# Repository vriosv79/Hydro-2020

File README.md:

Respositorio para velocímetros con códigos y diseños de PCB

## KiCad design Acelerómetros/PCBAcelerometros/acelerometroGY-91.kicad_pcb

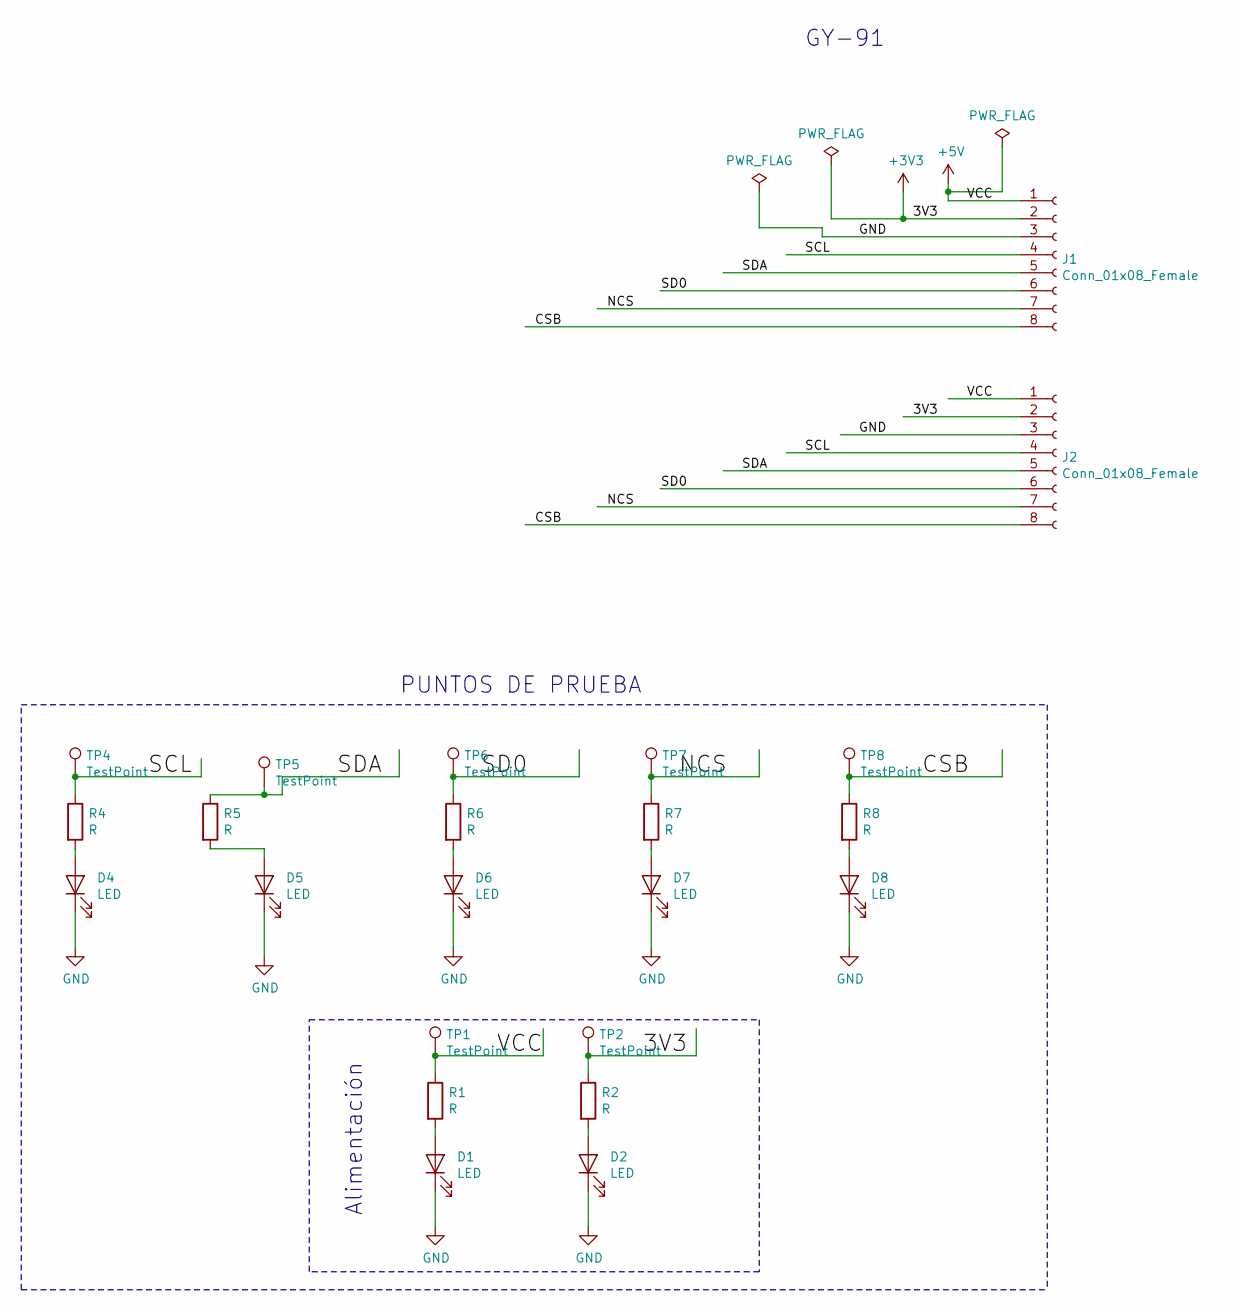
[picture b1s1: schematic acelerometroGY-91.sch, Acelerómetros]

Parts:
D1, D2, D4, D5, D6, D7, D8: LED; LED_0805_2012Metric
J1: Conn_01x08_Female; PinHeader_1x08_P2.54mm_Vertical
J2: Conn_01x08_Female; Molex_CLIK-Mate_502382-0870_1x08-1MP_P1.25mm_Vertical
R1, R2, R4, R5, R6, R7, R8: R; R_0805_2012Metric
TP1, TP2, TP4, TP5, TP6, TP7, TP8: TestPoint; TestPoint_Bridge_Pitch2.0mm_Drill0.7mm

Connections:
+3V3: J1.2, J2.2, R2.1, TP2.1
+5V: J1.1, J2.1, R1.1, TP1.1
/CSB: J1.8, J2.8, R8.1, TP8.1
/NCS: J1.7, J2.7, R7.1, TP7.1
/SCL: J1.4, J2.4, R4.1, TP4.1
/SD0: J1.6, J2.6, R6.1, TP6.1
/SDA: J1.5, J2.5, R5.1, TP5.1
GND: D1.1 (K), D2.1 (K), D4.1 (K), D5.1 (K), D6.1 (K), D7.1 (K), D8.1 (K), J1.3, J2.3
unnamed: D1.2 (A), R1.2
unnamed: D2.2 (A), R2.2
unnamed: D4.2 (A), R4.2
unnamed: D5.2 (A), R5.2
unnamed: D6.2 (A), R6.2
unnamed: D7.2 (A), R7.2
unnamed: D8.2 (A), R8.2

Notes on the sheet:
GY-91
PUNTOS DE PRUEBA
Alimentación

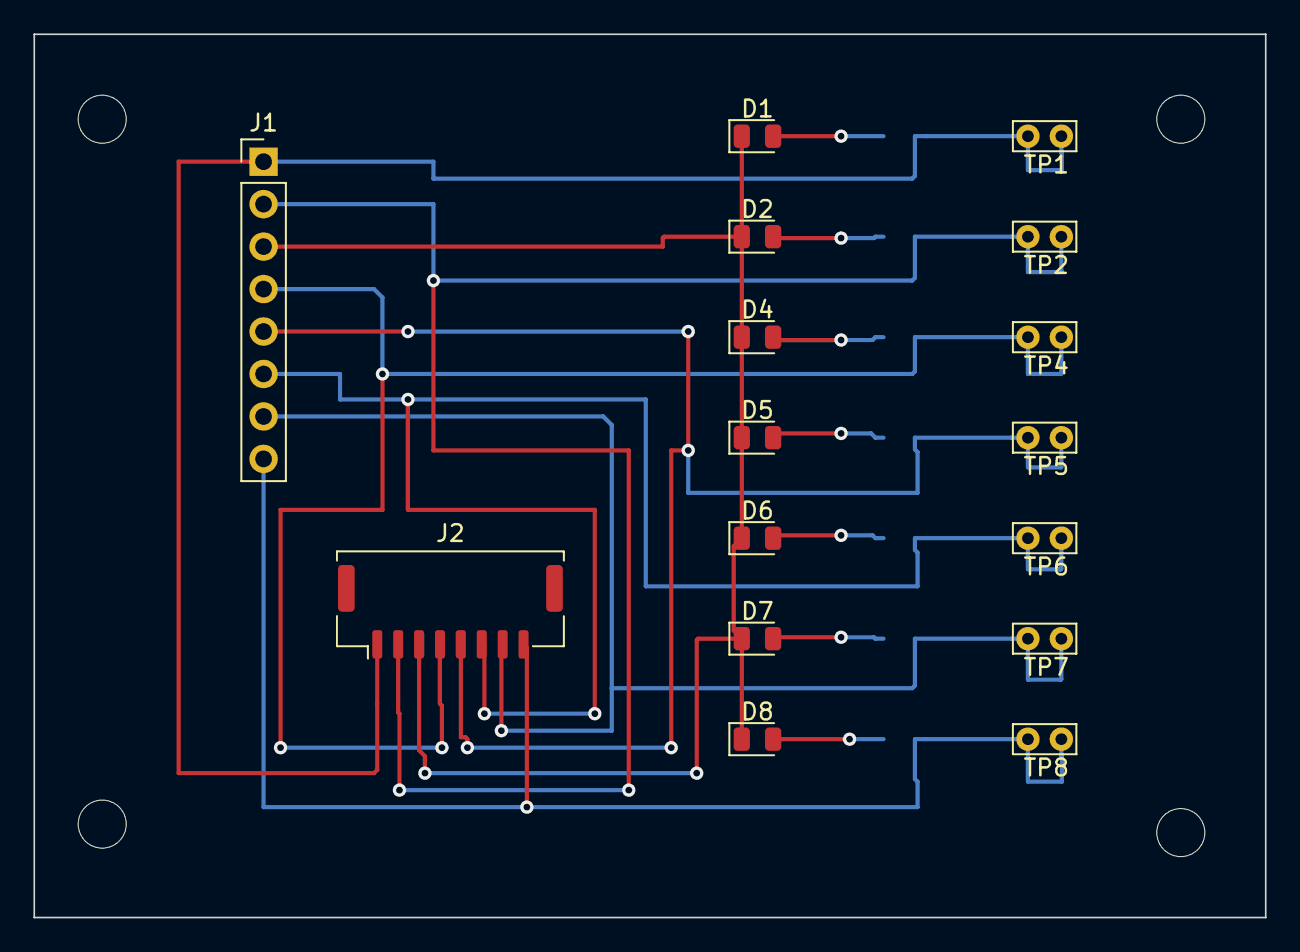
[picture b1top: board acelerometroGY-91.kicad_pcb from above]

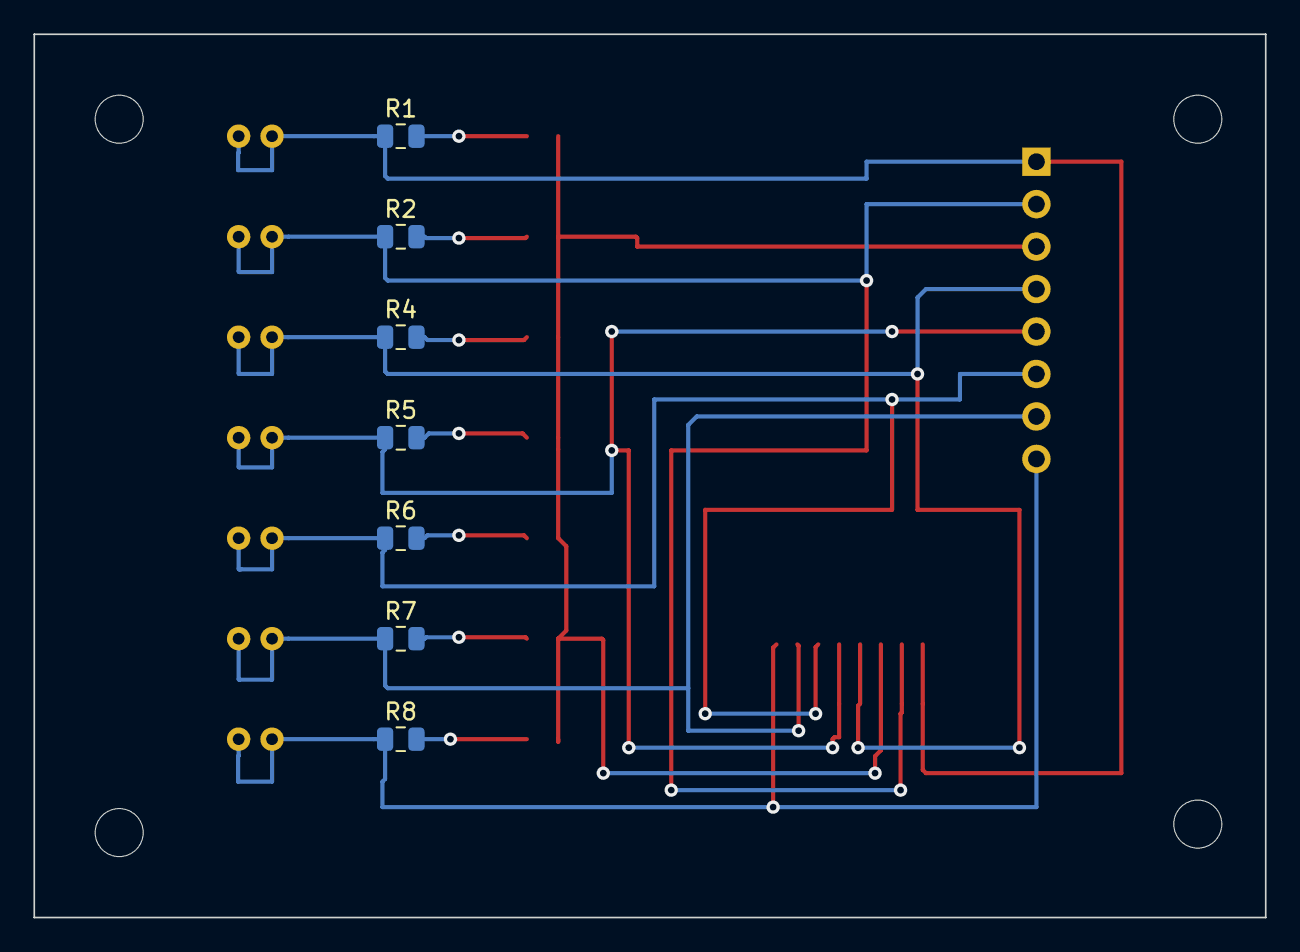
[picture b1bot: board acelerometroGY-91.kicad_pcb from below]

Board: 2 copper layers, 73.7 x 52.8 mm, 23 parts (7 on the bottom side), 15 nets.

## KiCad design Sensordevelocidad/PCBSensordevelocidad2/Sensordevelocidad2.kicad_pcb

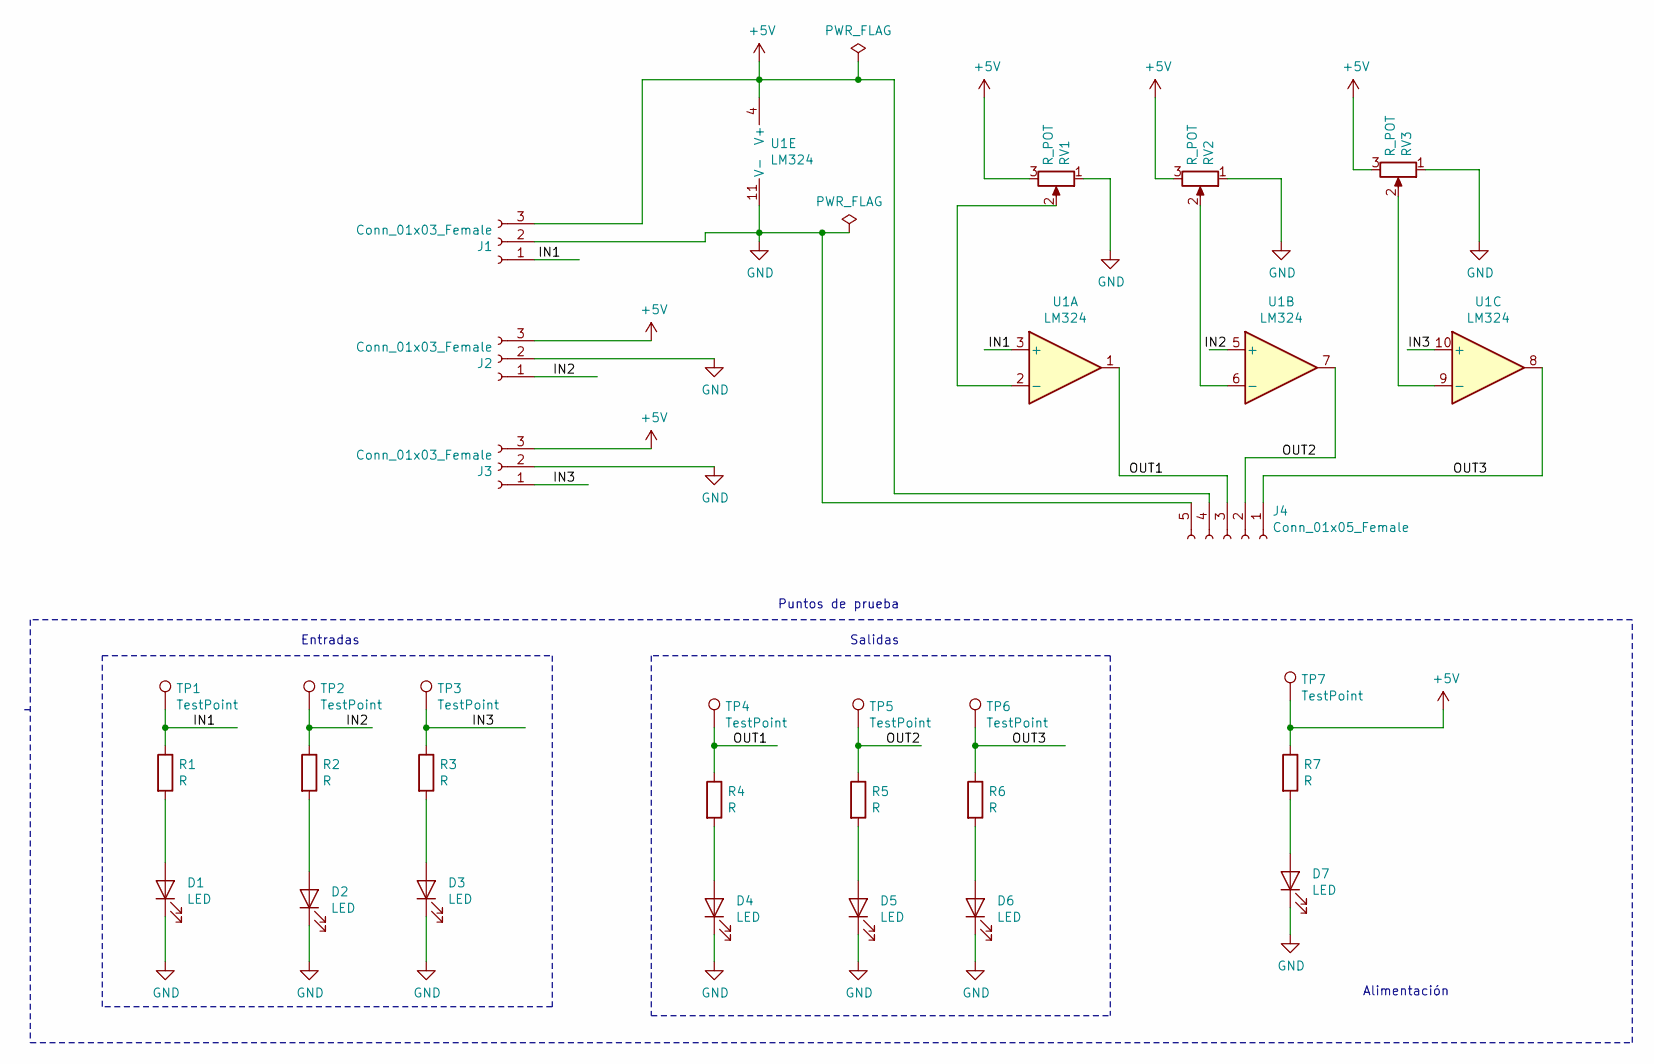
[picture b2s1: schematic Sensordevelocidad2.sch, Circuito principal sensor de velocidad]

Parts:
D1, D2, D3, D4, D5, D6, D7: LED; D_0805_2012Metric
J1, J2, J3: Conn_01x03_Female; Molex_Micro-Fit_3.0_43650-0315_1x03_P3.00mm_Vertical
J4: Conn_01x05_Female; Molex_CLIK-Mate_502443-0570_1x05-1MP_P2.00mm_Vertical
R1, R2, R3, R4, R5, R6, R7: R; R_0805_2012Metric
RV1, RV2, RV3: R_POT; Potentiometer_Bourns_3296Y_Vertical
TP1, TP2, TP3, TP4, TP5, TP6, TP7: TestPoint; TestPoint_Bridge_Pitch2.0mm_Drill0.7mm
U1: LM324; DIP-14_W10.16mm

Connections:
+5V: J1.3, J2.3, J3.3, J4.4, R7.1, RV1.3, RV2.3, RV3.3, TP7.1, U1.4 (V+)
/IN1: J1.1, R1.1, TP1.1, U1.3 (+)
/IN2: J2.1, R2.1, TP2.1, U1.5 (+)
/IN3: J3.1, R3.1, TP3.1, U1.10 (+)
/OUT1: J4.3, R4.1, TP4.1, U1.1
/OUT2: J4.2, R5.1, TP5.1, U1.7
/OUT3: J4.1, R6.1, TP6.1, U1.8
GND: D1.1 (K), D2.1 (K), D3.1 (K), D4.1 (K), D5.1 (K), D6.1 (K), D7.1 (K), J1.2, J2.2, J3.2, J4.5, RV1.1, RV2.1, RV3.1, U1.11 (V-)
unnamed: D1.2 (A), R1.2
unnamed: D2.2 (A), R2.2
unnamed: D3.2 (A), R3.2
unnamed: D4.2 (A), R4.2
unnamed: D5.2 (A), R5.2
unnamed: D6.2 (A), R6.2
unnamed: D7.2 (A), R7.2
unnamed: RV1.2, U1.2 (-)
unnamed: RV2.2, U1.6 (-)
unnamed: RV3.2, U1.9 (-)

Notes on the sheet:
Entradas
Salidas
Alimentación
Puntos de prueba

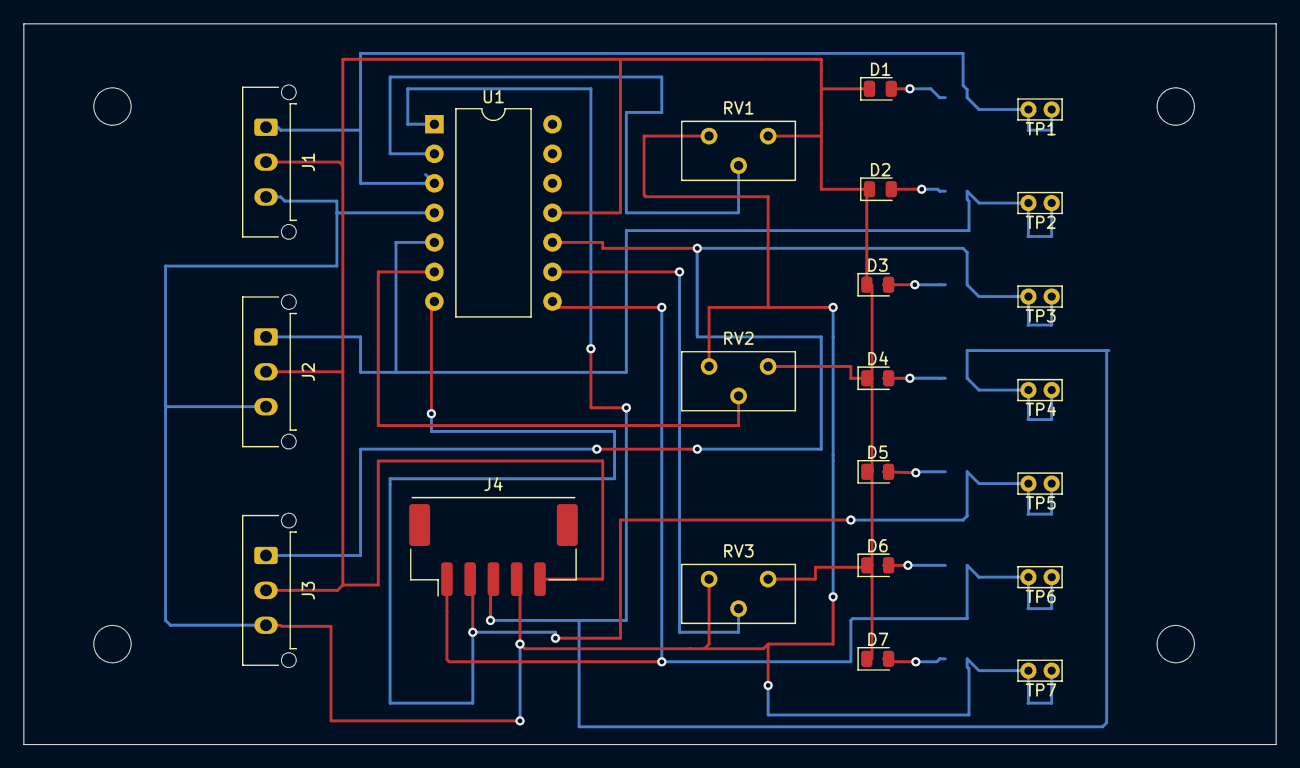
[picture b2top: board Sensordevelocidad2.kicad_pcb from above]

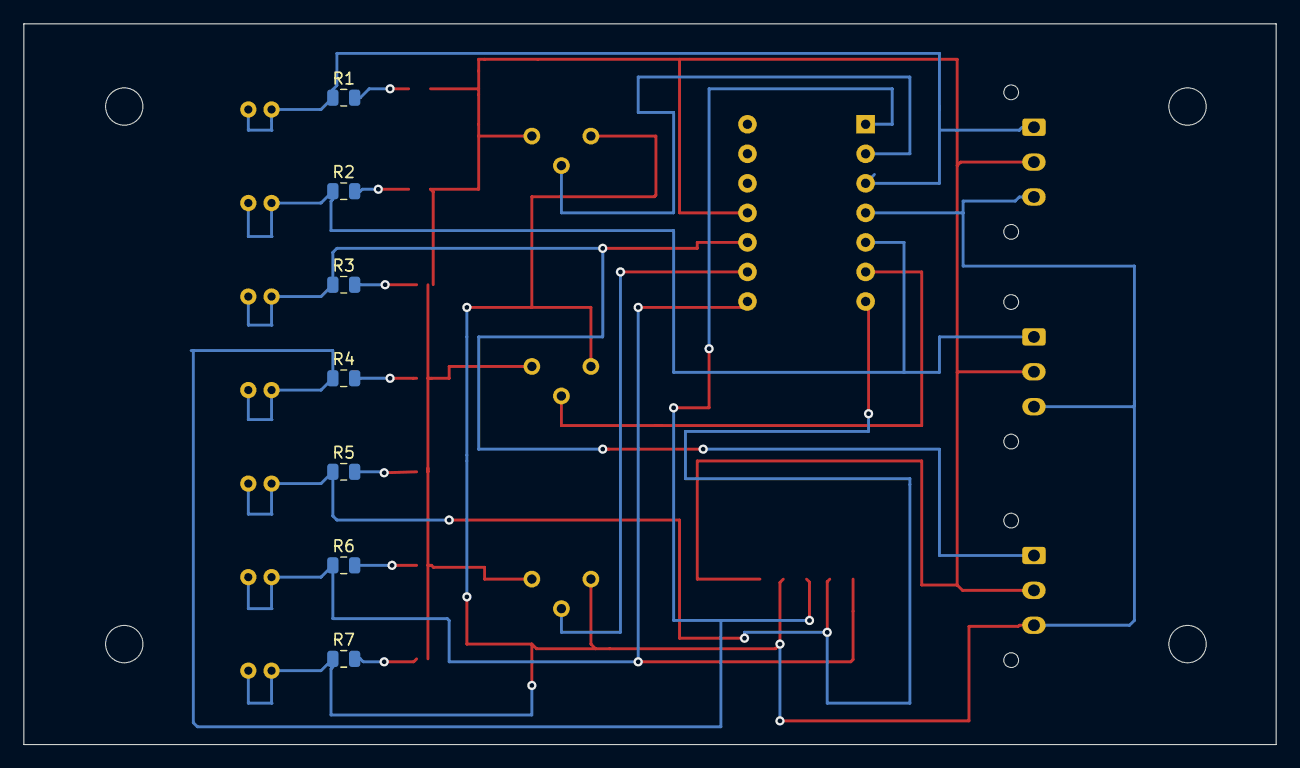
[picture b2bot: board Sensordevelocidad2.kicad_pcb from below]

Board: 2 copper layers, 107.7 x 62.0 mm, 29 parts (7 on the bottom side), 18 nets.

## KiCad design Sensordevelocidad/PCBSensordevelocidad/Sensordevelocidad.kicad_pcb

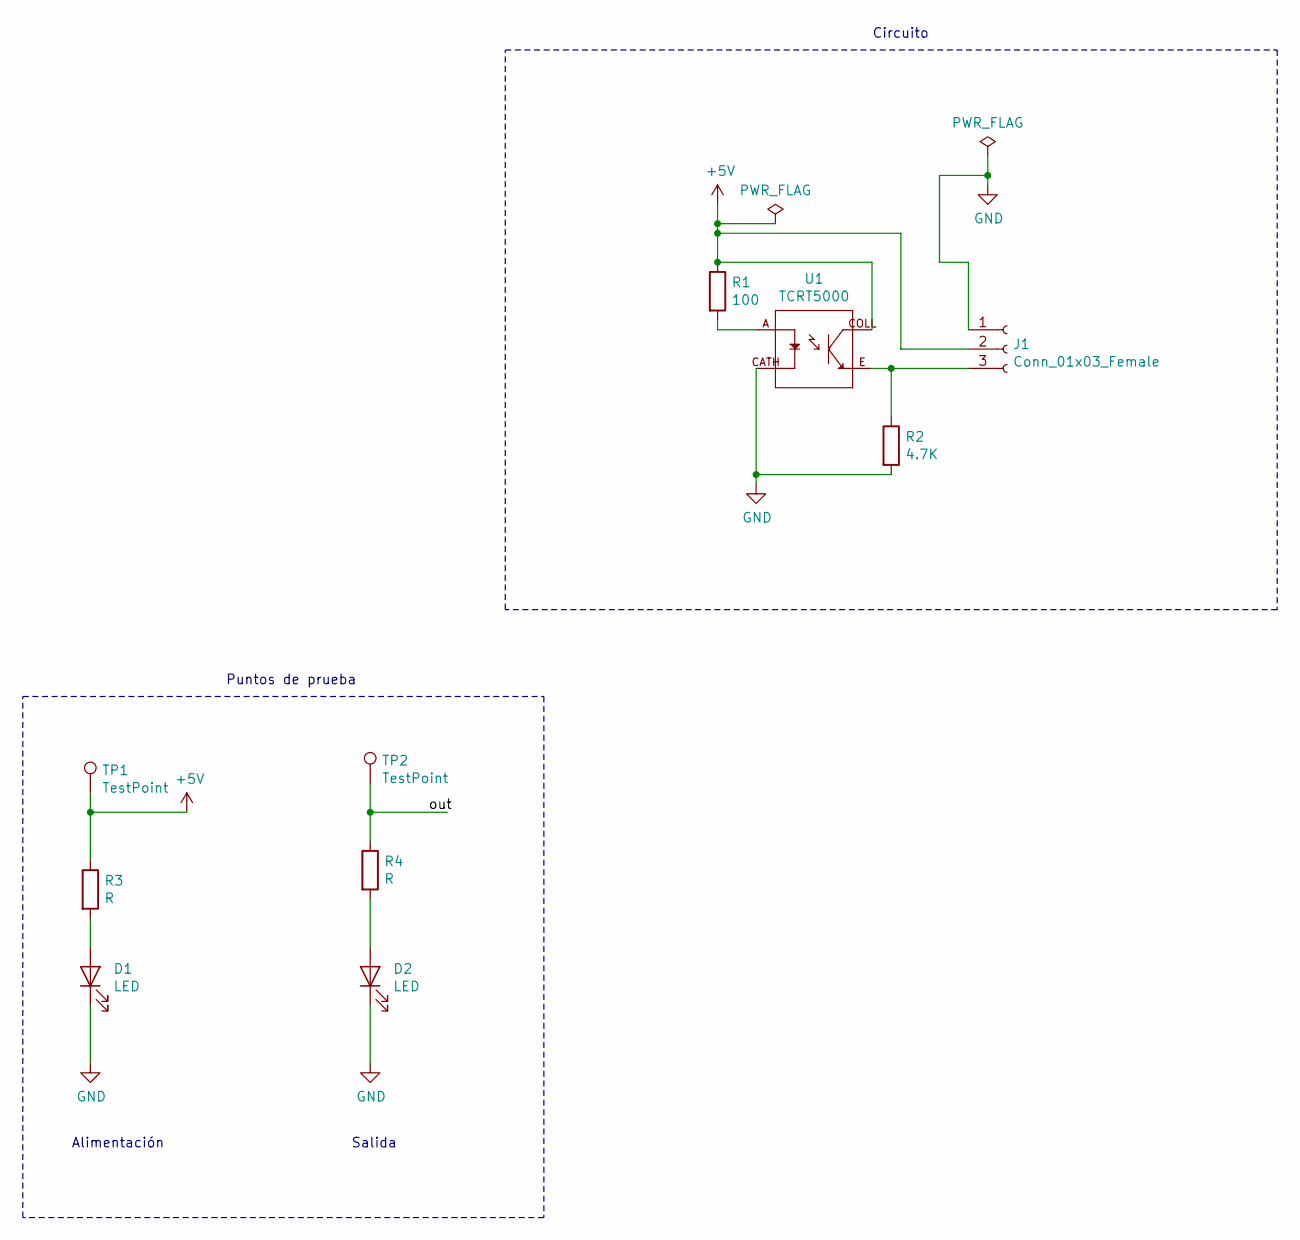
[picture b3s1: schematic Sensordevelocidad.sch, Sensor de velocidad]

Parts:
D1, D2: LED; LED_D3.0mm
J1: Conn_01x03_Female; Molex_CLIK-Mate_502382-0370_1x03-1MP_P1.25mm_Vertical
R1: 100; R_0805_2012Metric
R2: 4.7K; R_0805_2012Metric
R3, R4: R; R_0805_2012Metric
TP1, TP2: TestPoint; TestPoint_2Pads_Pitch2.54mm_Drill0.8mm
U1: TCRT5000; OPTO_TCRT5000

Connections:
+5V: J1.2, R1.1, R3.1, TP1.1, U1.COLL
/out: R4.1, TP2.1
GND: D1.1 (K), D2.1 (K), J1.1, R2.2, U1.CATH
unnamed: D1.2 (A), R3.2
unnamed: D2.2 (A), R4.2
unnamed: J1.3, R2.1, U1.E
unnamed: R1.2, U1.A

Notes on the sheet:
Puntos de prueba
Alimentación
Salida
Circuito

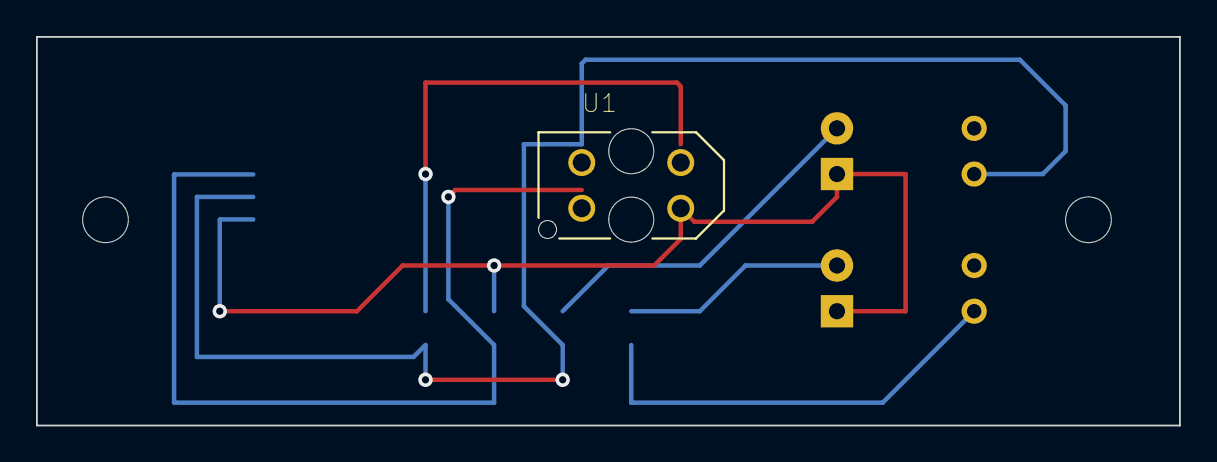
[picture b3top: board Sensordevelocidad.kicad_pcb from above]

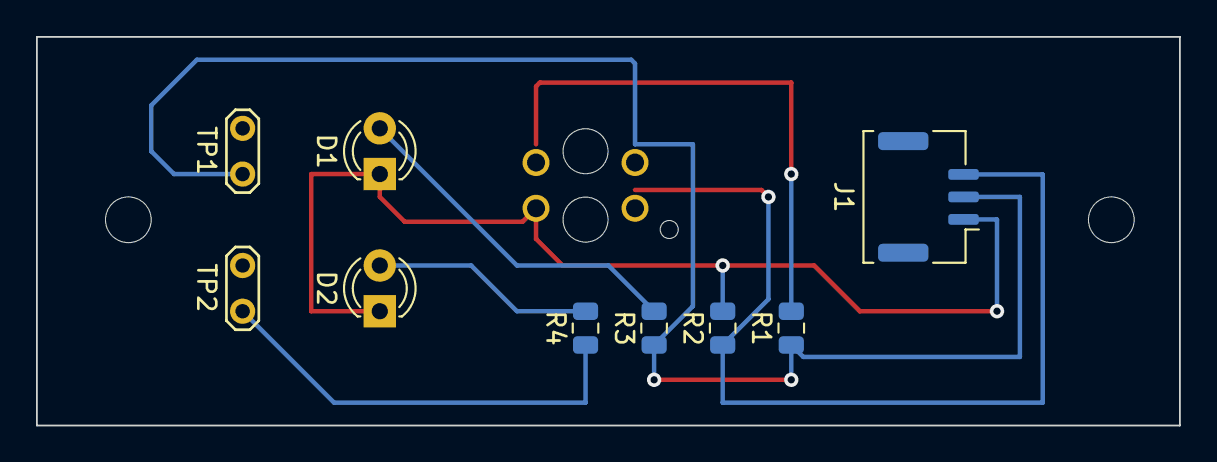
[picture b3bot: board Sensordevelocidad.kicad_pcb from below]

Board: 2 copper layers, 63.5 x 21.6 mm, 10 parts (9 on the bottom side), 7 nets.

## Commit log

2020-07-03 Se sube los sensores de velocidad
2020-07-03 Imagen PCB sensor de velocidad
2020-07-03 Imagen 2 de sensores de velocidad
2020-07-03 Código para el cálculo de rpm
2020-07-03 Archivos Kicad
2020-07-03 Librerias para código acelerómetros
2020-07-03 Codigo para calculo aceleración angular
2020-07-03 Codigo aceleracion angular arduino
2020-07-03 Imagen pcb
2020-07-03 Explicacion
